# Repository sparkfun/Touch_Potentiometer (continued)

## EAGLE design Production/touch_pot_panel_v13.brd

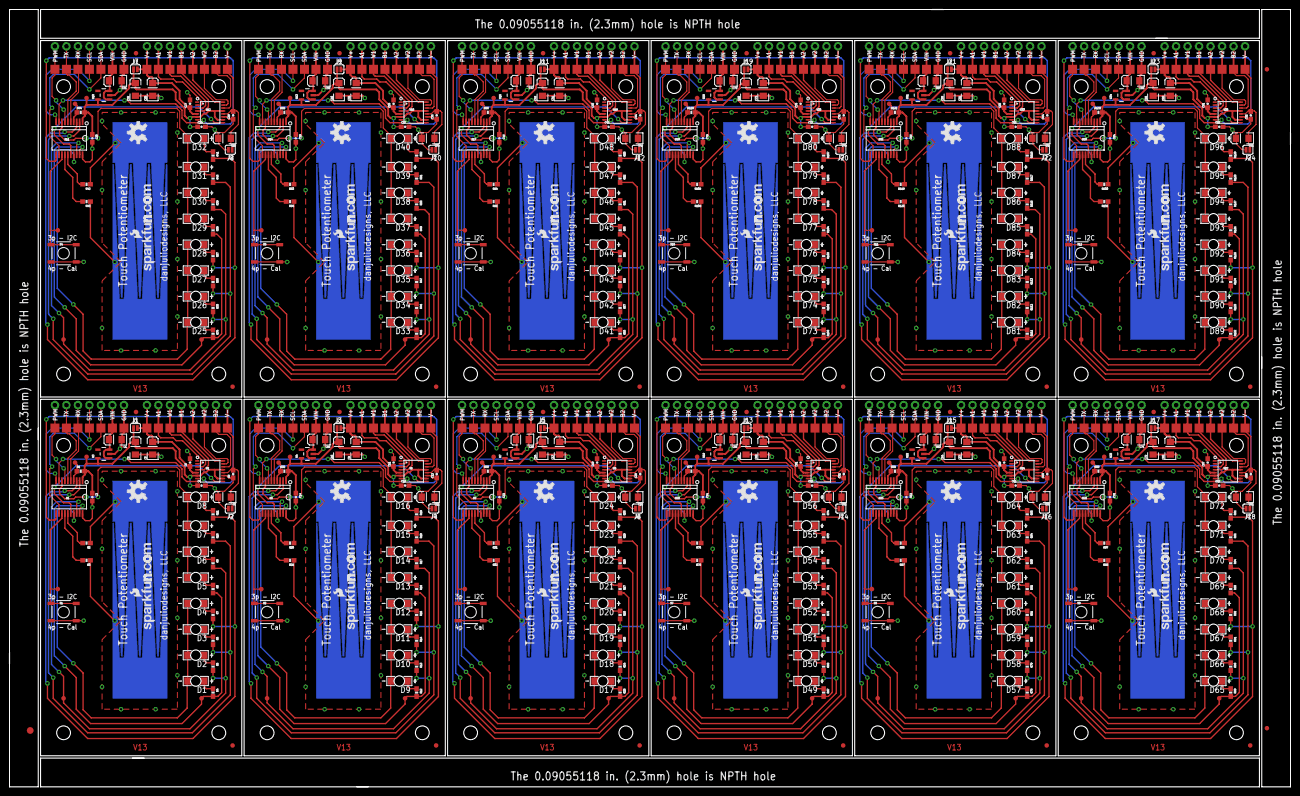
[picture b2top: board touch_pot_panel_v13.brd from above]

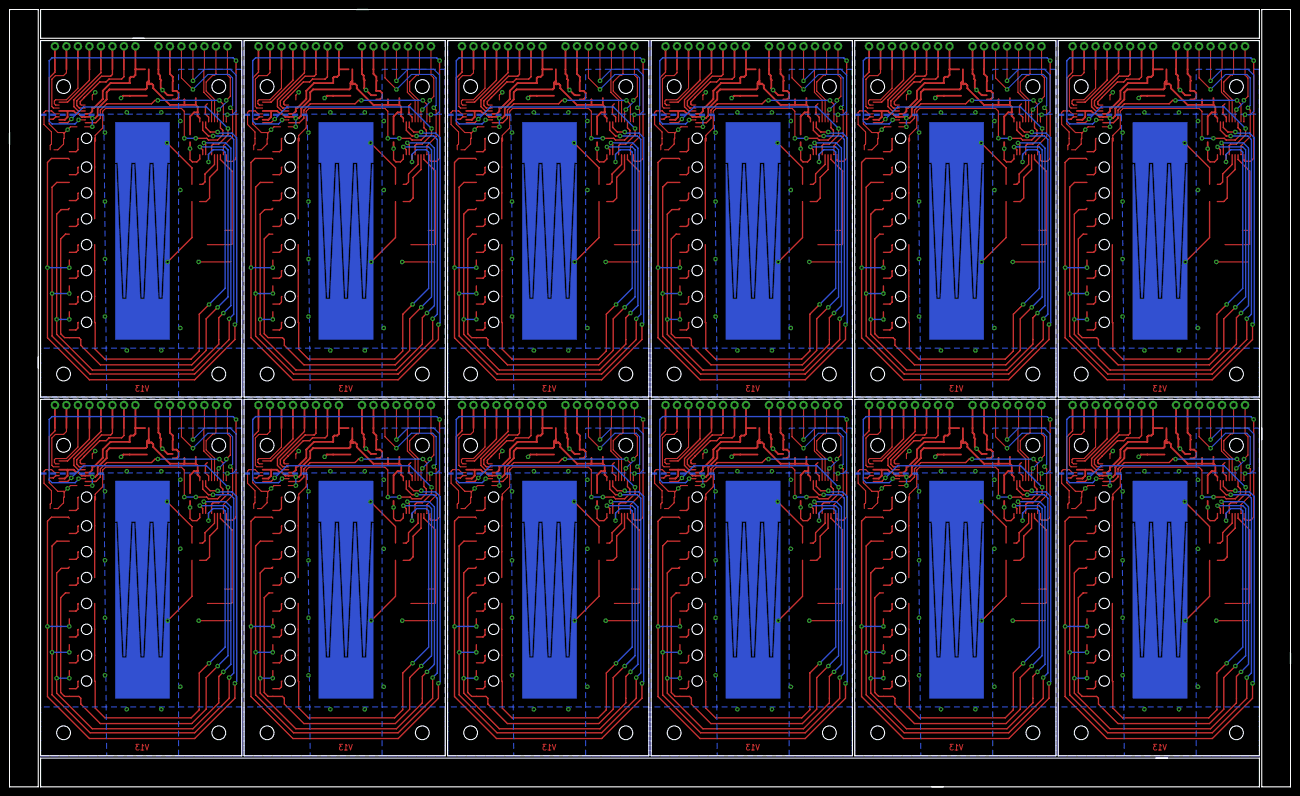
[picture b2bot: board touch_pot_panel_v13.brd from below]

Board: 2 copper layers, 283.0 x 171.7 mm, 927 parts (12 on the bottom side), 468 nets.

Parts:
C1, C2, C5, C7, C9, C10, C15, C16, C17, C18, C23, C24, C25, C26, C31, C32, C33, C34, C39, C40, C41, C42, C47, C48, C49, C50, C55, C56, C57, C58, C63, C64, C65, C66, C71, C72, C73, C74, C79, C80, C81, C82, C87, C88, C89, C90, C95, C96: 10uF; EIA3216
C3, C4, C6, C8, C11, C12, C13, C14, C19, C20, C21, C22, C27, C28, C29, C30, C35, C36, C37, C38, C43, C44, C45, C46, C51, C52, C53, C54, C59, C60, C61, C62, C67, C68, C69, C70, C75, C76, C77, C78, C83, C84, C85, C86, C91, C92, C93, C94: 0.1uF; 0603-CAP
D1, D2, D3, D4, D5, D6, D7, D8, D9, D10, D11, D12, D13, D14, D15, D16, D17, D18, D19, D20, D21, D22, D23, D24, D25, D26, D27, D28, D29, D30, D31, D32, D33, D34, D35, D36, D37, D38, D39, D40, D41, D42, D43, D44, D45, D46, D47, D48, D49, D50, D51, D52, D53, D54, D55, D56, D57, D58, D59, D60, D61, D62, D63, D64, D65, D66, D67, D68, D69, D70, D71, D72, D73, D74, D75, D76, D77, D78, D79, D80, D81, D82, D83, D84, D85, D86, D87, D88, D89, D90, D91, D92, D93, D94, D95, D96: Green; LED-1206-BOTTOM
E$1: FIDUCIAL-1.5X3
E$7, E$8: FIDUCIAL-1X2
FID1, FID2, FID3, FID4, FID5, FID6, FID7, FID8, FID9, FID10, FID11, FID12, FID13, FID14, FID15, FID16, FID17, FID18, FID19, FID20, FID21, FID22, FID23, FID24: FIDUCIAL1X2; FIDUCIAL-1X2
J1, J2, J3, J4, J5, J6, J7, J8, J9, J10, J11, J12, J13, J14, J15, J16, J17, J18, J19, J20, J21, J22, J23, J24: SJ_2S
JP1, JP2, JP3, JP4, JP5, JP6, JP7, JP8, JP9, JP10, JP11, JP12, JP13, JP14, JP15, JP16, JP17, JP18, JP19, JP20, JP21, JP22, JP23, JP24, JP25, JP26, JP27, JP28, JP29, JP30, JP31, JP32, JP33, JP34, JP35, JP36, JP37, JP38, JP39, JP40, JP41, JP42, JP43, JP44, JP45, JP46, JP47, JP48, JP49, JP50, JP51, JP52, JP53, JP54, JP55, JP56, JP57, JP58, JP59, JP60, JP61, JP62, JP63, JP64, JP65, JP66, JP67, JP68, JP69, JP70, JP71, JP72, JP73, JP74, JP75, JP76, JP77, JP78, JP79, JP80, JP81, JP82, JP83, JP84, JP85, JP86, JP87, JP88, JP89, JP90, JP91, JP92, JP93, JP94, JP95, JP96, JP97, JP98, JP99, JP100, JP101, JP102, JP103, JP104, JP105, JP106, JP107, JP108, JP109, JP110, JP111, JP112, JP113, JP114, JP115, JP116, JP117, JP118, JP119, JP120, JP121, JP122, JP123, JP124, JP125, JP126, JP127, JP128, JP129, JP130, JP131, JP132, JP133, JP134, JP135, JP136, JP137, JP138, JP139, JP140, JP141, JP142, JP143, JP144, JP145, JP146, JP147, JP148, JP149, JP150, JP151, JP152, JP153, JP154, JP155, JP156, JP157, JP158, JP159, JP160, JP161, JP162, JP163, JP164, JP165, JP166, JP167, JP168, JP169, JP170, JP171, JP172, JP173, JP174, JP175, JP176, JP177, JP178, JP179, JP180: 1X01NS
R1, R22, R33, R44, R55, R66, R77, R88, R99, R110, R121, R132: 10K; 0603-RES
R2, R3, R4, R5, R6, R7, R8, R9, R10, R11, R12, R13, R14, R15, R16, R17, R18, R19, R20, R21, R23, R24, R25, R26, R27, R28, R29, R30, R31, R32, R34, R35, R36, R37, R38, R39, R40, R41, R42, R43, R45, R46, R47, R48, R49, R50, R51, R52, R53, R54, R56, R57, R58, R59, R60, R61, R62, R63, R64, R65, R67, R68, R69, R70, R71, R72, R73, R74, R75, R76, R78, R79, R80, R81, R82, R83, R84, R85, R86, R87, R89, R90, R91, R92, R93, R94, R95, R96, R97, R98, R100, R101, R102, R103, R104, R105, R106, R107, R108, R109, R111, R112, R113, R114, R115, R116, R117, R118, R119, R120, R122, R123, R124, R125, R126, R127, R128, R129, R130, R131: 100; 0603-RES
S1, S2, S3, S4, S5, S6, S7, S8, S9, S10, S11, S12: TACTILE-SWITCH-SMD
STANDOFF1, STANDOFF2, STANDOFF3, STANDOFF4, STANDOFF5, STANDOFF6, STANDOFF7, STANDOFF8, STANDOFF9, STANDOFF10, STANDOFF11, STANDOFF12, STANDOFF13, STANDOFF14, STANDOFF15, STANDOFF16, STANDOFF17, STANDOFF18, STANDOFF19, STANDOFF20, STANDOFF21, STANDOFF22, STANDOFF23, STANDOFF24, STANDOFF25, STANDOFF26, STANDOFF27, STANDOFF28, STANDOFF29, STANDOFF30, STANDOFF31, STANDOFF32, STANDOFF33, STANDOFF34, STANDOFF35, STANDOFF36, STANDOFF37, STANDOFF38, STANDOFF39, STANDOFF40, STANDOFF41, STANDOFF42, STANDOFF43, STANDOFF44, STANDOFF45, STANDOFF46, STANDOFF47, STANDOFF48: STAND-OFFTIGHT; STAND-OFF-TIGHT
TP1, TP2, TP3, TP4, TP5, TP36, TP37, TP38, TP39, TP40, TP56, TP57, TP58, TP59, TP60, TP76, TP77, TP78, TP79, TP80, TP96, TP97, TP98, TP99, TP100, TP116, TP117, TP118, TP119, TP120, TP136, TP137, TP138, TP139, TP140, TP156, TP157, TP158, TP159, TP160, TP176, TP177, TP178, TP179, TP180, TP196, TP197, TP198, TP199, TP200, TP216, TP217, TP218, TP219, TP220, TP236, TP237, TP238, TP239, TP240: PAD.03X.04
TP6, TP7, TP8, TP9, TP10, TP11, TP12, TP13, TP14, TP15, TP16, TP17, TP18, TP19, TP20, TP21, TP22, TP23, TP24, TP25, TP26, TP27, TP28, TP29, TP30, TP31, TP32, TP33, TP34, TP35, TP41, TP42, TP43, TP44, TP45, TP46, TP47, TP48, TP49, TP50, TP51, TP52, TP53, TP54, TP55, TP61, TP62, TP63, TP64, TP65, TP66, TP67, TP68, TP69, TP70, TP71, TP72, TP73, TP74, TP75, TP81, TP82, TP83, TP84, TP85, TP86, TP87, TP88, TP89, TP90, TP91, TP92, TP93, TP94, TP95, TP101, TP102, TP103, TP104, TP105, TP106, TP107, TP108, TP109, TP110, TP111, TP112, TP113, TP114, TP115, TP121, TP122, TP123, TP124, TP125, TP126, TP127, TP128, TP129, TP130, TP131, TP132, TP133, TP134, TP135, TP141, TP142, TP143, TP144, TP145, TP146, TP147, TP148, TP149, TP150, TP151, TP152, TP153, TP154, TP155, TP161, TP162, TP163, TP164, TP165, TP166, TP167, TP168, TP169, TP170, TP171, TP172, TP173, TP174, TP175, TP181, TP182, TP183, TP184, TP185, TP186, TP187, TP188, TP189, TP190, TP191, TP192, TP193, TP194, TP195, TP201, TP202, TP203, TP204, TP205, TP206, TP207, TP208, TP209, TP210, TP211, TP212, TP213, TP214, TP215, TP221, TP222, TP223, TP224, TP225, TP226, TP227, TP228, TP229, TP230, TP231, TP232, TP233, TP234, TP235: 2MM_SMD_PAD
TS1, TS2, TS3, TS4, TS5, TS6, TS7, TS8, TS9, TS10, TS11, TS12: 2CH_48MM_LINEAR_TOUCH
U1, U5, U8, U11, U14, U17, U20, U23, U26, U29, U32, U35: PIC16F1829; SSOP20
U2, U6, U9, U12, U15, U18, U21, U24, U27, U30, U33, U36: AD5262; SSOP16
U3, U4, U7, U10, U13, U16, U19, U22, U25, U28, U31, U34: 5V; SOT23-5
U$1, U$3, U$4, U$7, U$9, U$11, U$13, U$15, U$17, U$19, U$21, U$23: OSHW-LOGOM; OSHW-LOGO-M
U$2, U$5, U$6, U$8, U$10, U$12, U$14, U$16, U$18, U$20, U$22, U$24: SFE_LOGO_NAME_WEB; SFE-NEW-WEBLOGO

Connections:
+5V: C2.A, C3.1, C4.1, J1.1, R1.2, TP2.P$1, U1.1, U2.6, U2.10, U2.13, U3.5
+5V1: C13.1, C14.1, C16.A, J3.1, R22.2, TP36.P$1, U4.5, U5.1, U6.6, U6.10, U6.13
+5V2: C21.1, C22.1, C24.A, J5.1, R33.2, TP56.P$1, U7.5, U8.1, U9.6, U9.10, U9.13
+5V3: C29.1, C30.1, C32.A, J7.1, R44.2, TP76.P$1, U10.5, U11.1, U12.6, U12.10, U12.13
+5V4: C37.1, C38.1, C40.A, J9.1, R55.2, TP96.P$1, U13.5, U14.1, U15.6, U15.10, U15.13
+5V5: C45.1, C46.1, C48.A, J11.1, R66.2, TP116.P$1, U16.5, U17.1, U18.6, U18.10, U18.13
+5V6: C53.1, C54.1, C56.A, J13.1, R77.2, TP136.P$1, U19.5, U20.1, U21.6, U21.10, U21.13
+5V7: C61.1, C62.1, C64.A, J15.1, R88.2, TP156.P$1, U22.5, U23.1, U24.6, U24.10, U24.13
+5V8: C69.1, C70.1, C72.A, J17.1, R99.2, TP176.P$1, U25.5, U26.1, U27.6, U27.10, U27.13
+5V9: C77.1, C78.1, C80.A, J19.1, R110.2, TP196.P$1, U28.5, U29.1, U30.6, U30.10, U30.13
+5V10: C85.1, C86.1, C88.A, J21.1, R121.2, TP216.P$1, U31.5, U32.1, U33.6, U33.10, U33.13
+5V11: C93.1, C94.1, C96.A, J23.1, R132.2, TP236.P$1, U34.5, U35.1, U36.6, U36.10, U36.13
A1: JP14.1, TP19.P$1, U2.2
A2: JP11.1, TP16.P$1, U2.16
A3: JP29.1, TP34.P$1, U6.2
A4: JP26.1, TP31.P$1, U6.16
A5: JP44.1, TP54.P$1, U9.2
A6: JP41.1, TP51.P$1, U9.16
A7: JP59.1, TP74.P$1, U12.2
A8: JP56.1, TP71.P$1, U12.16
A9: JP74.1, TP94.P$1, U15.2
A10: JP71.1, TP91.P$1, U15.16
A11: JP89.1, TP114.P$1, U18.2
A12: JP86.1, TP111.P$1, U18.16
A13: JP104.1, TP134.P$1, U21.2
A14: JP101.1, TP131.P$1, U21.16
A15: JP119.1, TP154.P$1, U24.2
A16: JP116.1, TP151.P$1, U24.16
A17: JP134.1, TP174.P$1, U27.2
A18: JP131.1, TP171.P$1, U27.16
A19: JP149.1, TP194.P$1, U30.2
A20: JP146.1, TP191.P$1, U30.16
A21: JP164.1, TP214.P$1, U33.2
A22: JP161.1, TP211.P$1, U33.16
A23: JP179.1, TP234.P$1, U36.2
A24: JP176.1, TP231.P$1, U36.16
AUX: S1.1, TP3.P$1, U1.13
AUX1: S2.1, TP37.P$1, U5.13
AUX2: S3.1, TP57.P$1, U8.13
AUX3: S4.1, TP77.P$1, U11.13
AUX4: S5.1, TP97.P$1, U14.13
AUX5: S6.1, TP117.P$1, U17.13
AUX6: S7.1, TP137.P$1, U20.13
AUX7: S8.1, TP157.P$1, U23.13
AUX8: S9.1, TP177.P$1, U26.13
AUX9: S10.1, TP197.P$1, U29.13
AUX10: S11.1, TP217.P$1, U32.13
AUX11: S12.1, TP237.P$1, U35.13
B1: JP12.1, TP17.P$1, U2.4
B2: JP9.1, TP14.P$1, U2.14
B3: JP27.1, TP32.P$1, U6.4
B4: JP24.1, TP29.P$1, U6.14
B5: JP42.1, TP52.P$1, U9.4
B6: JP39.1, TP49.P$1, U9.14
B7: JP57.1, TP72.P$1, U12.4
B8: JP54.1, TP69.P$1, U12.14
B9: JP72.1, TP92.P$1, U15.4
B10: JP69.1, TP89.P$1, U15.14
B11: JP87.1, TP112.P$1, U18.4
B12: JP84.1, TP109.P$1, U18.14
B13: JP102.1, TP132.P$1, U21.4
B14: JP99.1, TP129.P$1, U21.14
B15: JP117.1, TP152.P$1, U24.4
B16: JP114.1, TP149.P$1, U24.14
B17: JP132.1, TP172.P$1, U27.4
B18: JP129.1, TP169.P$1, U27.14
B19: JP147.1, TP192.P$1, U30.4
B20: JP144.1, TP189.P$1, U30.14
B21: JP162.1, TP212.P$1, U33.4
B22: JP159.1, TP209.P$1, U33.14
B23: JP177.1, TP232.P$1, U36.4
B24: JP174.1, TP229.P$1, U36.14
CPAD1: R3.2, U1.14
CPAD2: R2.2, U1.15
CPAD3: R21.2, U5.14
CPAD4: R20.2, U5.15
CPAD5: R32.2, U8.14
CPAD6: R31.2, U8.15
CPAD7: R43.2, U11.14
CPAD8: R42.2, U11.15
CPAD9: R54.2, U14.14
CPAD10: R53.2, U14.15
CPAD11: R65.2, U17.14
CPAD12: R64.2, U17.15
CPAD13: R76.2, U20.14
CPAD14: R75.2, U20.15
CPAD15: R87.2, U23.14
CPAD16: R86.2, U23.15
CPAD17: R98.2, U26.14
CPAD18: R97.2, U26.15
CPAD19: R109.2, U29.14
CPAD20: R108.2, U29.15
CPAD21: R120.2, U32.14
CPAD22: R119.2, U32.15
CPAD23: R131.2, U35.14
CPAD24: R130.2, U35.15
CSN: U1.16, U2.9
CSN1: U5.16, U6.9
CSN2: U8.16, U9.9
CSN3: U11.16, U12.9
CSN4: U14.16, U15.9
CSN5: U17.16, U18.9
CSN6: U20.16, U21.9
CSN7: U23.16, U24.9
CSN8: U26.16, U27.9
CSN9: U29.16, U30.9
CSN10: U32.16, U33.9
CSN11: U35.16, U36.9
GND: C1.C, C2.C, C3.2, C4.2, C5.C, C6.2, C7.A, C8.1, J2.1, JP7.1, S1.3, TP12.P$1, U1.20, U2.11, U3.2
GND1: C9.C, C10.A, C11.2, C12.1, C13.2, C14.2, C15.C, C16.C, J4.1, JP22.1, S2.3, TP27.P$1, U4.2, U5.20, U6.11
GND2: C17.C, C18.A, C19.2, C20.1, C21.2, C22.2, C23.C, C24.C, J6.1, JP37.1, S3.3, TP47.P$1, U7.2, U8.20, U9.11
GND3: C25.C, C26.A, C27.2, C28.1, C29.2, C30.2, C31.C, C32.C, J8.1, JP52.1, S4.3, TP67.P$1, U10.2, U11.20, U12.11
GND4: C33.C, C34.A, C35.2, C36.1, C37.2, C38.2, C39.C, C40.C, J10.1, JP67.1, S5.3, TP87.P$1, U13.2, U14.20, U15.11
GND5: C41.C, C42.A, C43.2, C44.1, C45.2, C46.2, C47.C, C48.C, J12.1, JP82.1, S6.3, TP107.P$1, U16.2, U17.20, U18.11
GND6: C49.C, C50.A, C51.2, C52.1, C53.2, C54.2, C55.C, C56.C, J14.1, JP97.1, S7.3, TP127.P$1, U19.2, U20.20, U21.11
GND7: C57.C, C58.A, C59.2, C60.1, C61.2, C62.2, C63.C, C64.C, J16.1, JP112.1, S8.3, TP147.P$1, U22.2, U23.20, U24.11
GND8: C65.C, C66.A, C67.2, C68.1, C69.2, C70.2, C71.C, C72.C, J18.1, JP127.1, S9.3, TP167.P$1, U25.2, U26.20, U27.11
GND9: C73.C, C74.A, C75.2, C76.1, C77.2, C78.2, C79.C, C80.C, J20.1, JP142.1, S10.3, TP187.P$1, U28.2, U29.20, U30.11
GND10: C81.C, C82.A, C83.2, C84.1, C85.2, C86.2, C87.C, C88.C, J22.1, JP157.1, S11.3, TP207.P$1, U31.2, U32.20, U33.11
GND11: C89.C, C90.A, C91.2, C92.1, C93.2, C94.2, C95.C, C96.C, J24.1, JP172.1, S12.3, TP227.P$1, U34.2, U35.20, U36.11
LA0: R4.2, R8.2, TP4.P$1, U1.19
LA1: R5.2, R9.2, TP5.P$1, U1.18
LA2: R6.2, R10.2, U1.2
LA3: R7.2, R11.2, U1.3
LA4: R14.2, R18.2, U5.2
LA5: R15.2, R19.2, U5.3
LA6: R13.2, R17.2, TP40.P$1, U5.18
LA7: R12.2, R16.2, TP39.P$1, U5.19
LA8: R25.2, R29.2, U8.2
LA9: R26.2, R30.2, U8.3
LA10: R24.2, R28.2, TP60.P$1, U8.18
LA11: R23.2, R27.2, TP59.P$1, U8.19
LA12: R36.2, R40.2, U11.2
LA13: R37.2, R41.2, U11.3
LA14: R35.2, R39.2, TP80.P$1, U11.18
LA15: R34.2, R38.2, TP79.P$1, U11.19
LA16: R47.2, R51.2, U14.2
LA17: R48.2, R52.2, U14.3
LA18: R46.2, R50.2, TP100.P$1, U14.18
LA19: R45.2, R49.2, TP99.P$1, U14.19
LA20: R58.2, R62.2, U17.2
LA21: R59.2, R63.2, U17.3
LA22: R57.2, R61.2, TP120.P$1, U17.18
LA23: R56.2, R60.2, TP119.P$1, U17.19
LA24: R69.2, R73.2, U20.2
LA25: R70.2, R74.2, U20.3
LA26: R68.2, R72.2, TP140.P$1, U20.18
LA27: R67.2, R71.2, TP139.P$1, U20.19
LA28: R80.2, R84.2, U23.2
LA29: R81.2, R85.2, U23.3
LA30: R79.2, R83.2, TP160.P$1, U23.18
LA31: R78.2, R82.2, TP159.P$1, U23.19
LA32: R91.2, R95.2, U26.2
LA33: R92.2, R96.2, U26.3
LA34: R90.2, R94.2, TP180.P$1, U26.18
LA35: R89.2, R93.2, TP179.P$1, U26.19
LA36: R102.2, R106.2, U29.2
LA37: R103.2, R107.2, U29.3
LA38: R101.2, R105.2, TP200.P$1, U29.18
LA39: R100.2, R104.2, TP199.P$1, U29.19
LA40: R113.2, R117.2, U32.2
LA41: R114.2, R118.2, U32.3
LA42: R112.2, R116.2, TP220.P$1, U32.18
LA43: R111.2, R115.2, TP219.P$1, U32.19
LA44: R124.2, R128.2, U35.2
LA45: R125.2, R129.2, U35.3
LA46: R123.2, R127.2, TP240.P$1, U35.18
LA47: R122.2, R126.2, TP239.P$1, U35.19
LED_PWM1: D1.C, D2.C, D3.C, D4.C, U1.17
LED_PWM2: D5.C, D6.C, D7.C, D8.C, U1.8
LED_PWM3: D9.C, D10.C, D11.C, D12.C, U5.17
LED_PWM4: D13.C, D14.C, D15.C, D16.C, U5.8
LED_PWM5: D17.C, D18.C, D19.C, D20.C, U8.17
LED_PWM6: D21.C, D22.C, D23.C, D24.C, U8.8
LED_PWM7: D25.C, D26.C, D27.C, D28.C, U11.17
LED_PWM8: D29.C, D30.C, D31.C, D32.C, U11.8
LED_PWM9: D33.C, D34.C, D35.C, D36.C, U14.17
LED_PWM10: D37.C, D38.C, D39.C, D40.C, U14.8
LED_PWM11: D41.C, D42.C, D43.C, D44.C, U17.17
LED_PWM12: D45.C, D46.C, D47.C, D48.C, U17.8
LED_PWM13: D49.C, D50.C, D51.C, D52.C, U20.17
LED_PWM14: D53.C, D54.C, D55.C, D56.C, U20.8
LED_PWM15: D57.C, D58.C, D59.C, D60.C, U23.17
LED_PWM16: D61.C, D62.C, D63.C, D64.C, U23.8
LED_PWM17: D65.C, D66.C, D67.C, D68.C, U26.17
LED_PWM18: D69.C, D70.C, D71.C, D72.C, U26.8
LED_PWM19: D73.C, D74.C, D75.C, D76.C, U29.17
LED_PWM20: D77.C, D78.C, D79.C, D80.C, U29.8
LED_PWM21: D81.C, D82.C, D83.C, D84.C, U32.17
LED_PWM22: D85.C, D86.C, D87.C, D88.C, U32.8
LED_PWM23: D89.C, D90.C, D91.C, D92.C, U35.17
LED_PWM24: D93.C, D94.C, D95.C, D96.C, U35.8
unnamed: D1.A, R4.1
unnamed: D2.A, R5.1
unnamed: D3.A, R6.1
unnamed: D4.A, R7.1
unnamed: D5.A, R8.1
unnamed: D6.A, R9.1
unnamed: D7.A, R10.1
unnamed: D8.A, R11.1
unnamed: R20.1, TS2.P$2
unnamed: R21.1, TS2.P$1
unnamed: D9.A, R12.1
unnamed: D10.A, R13.1
unnamed: D11.A, R14.1
unnamed: D12.A, R15.1
unnamed: D13.A, R16.1
unnamed: D14.A, R17.1
unnamed: D15.A, R18.1
unnamed: D16.A, R19.1
unnamed: R31.1, TS3.P$2
unnamed: R32.1, TS3.P$1
unnamed: D17.A, R23.1
unnamed: D18.A, R24.1
unnamed: D19.A, R25.1
unnamed: D20.A, R26.1
unnamed: D21.A, R27.1
unnamed: D22.A, R28.1
unnamed: D23.A, R29.1
unnamed: D24.A, R30.1
unnamed: R42.1, TS4.P$2
unnamed: R43.1, TS4.P$1
unnamed: R2.1, TS1.P$2
unnamed: R3.1, TS1.P$1
unnamed: D25.A, R34.1
unnamed: D26.A, R35.1
unnamed: D27.A, R36.1
unnamed: D28.A, R37.1
unnamed: D29.A, R38.1
unnamed: D30.A, R39.1
unnamed: D31.A, R40.1
unnamed: D32.A, R41.1
unnamed: R53.1, TS5.P$2
unnamed: R54.1, TS5.P$1
unnamed: D33.A, R45.1
unnamed: D34.A, R46.1
unnamed: D35.A, R47.1
unnamed: D36.A, R48.1
unnamed: D37.A, R49.1
unnamed: D38.A, R50.1
unnamed: D39.A, R51.1
unnamed: D40.A, R52.1
unnamed: R64.1, TS6.P$2
unnamed: R65.1, TS6.P$1
unnamed: D41.A, R56.1
unnamed: D42.A, R57.1
unnamed: D43.A, R58.1
unnamed: D44.A, R59.1
unnamed: D45.A, R60.1
unnamed: D46.A, R61.1
unnamed: D47.A, R62.1
unnamed: D48.A, R63.1
unnamed: R75.1, TS7.P$2
unnamed: R76.1, TS7.P$1
unnamed: D49.A, R67.1
unnamed: D50.A, R68.1
unnamed: D51.A, R69.1
unnamed: D52.A, R70.1
unnamed: D53.A, R71.1
unnamed: D54.A, R72.1
unnamed: D55.A, R73.1
unnamed: D56.A, R74.1
unnamed: R86.1, TS8.P$2
unnamed: R87.1, TS8.P$1
unnamed: D57.A, R78.1
unnamed: D58.A, R79.1
unnamed: D59.A, R80.1
unnamed: D60.A, R81.1
unnamed: D61.A, R82.1
unnamed: D62.A, R83.1
unnamed: D63.A, R84.1
unnamed: D64.A, R85.1
unnamed: R97.1, TS9.P$2
unnamed: R98.1, TS9.P$1
unnamed: D65.A, R89.1
unnamed: D66.A, R90.1
unnamed: D67.A, R91.1
unnamed: D68.A, R92.1
unnamed: D69.A, R93.1
unnamed: D70.A, R94.1
unnamed: D71.A, R95.1
unnamed: D72.A, R96.1
unnamed: R108.1, TS10.P$2
unnamed: R109.1, TS10.P$1
unnamed: D73.A, R100.1
unnamed: D74.A, R101.1
unnamed: D75.A, R102.1
unnamed: D76.A, R103.1
unnamed: D77.A, R104.1
unnamed: D78.A, R105.1
unnamed: D79.A, R106.1
unnamed: D80.A, R107.1
unnamed: R119.1, TS11.P$2
unnamed: R120.1, TS11.P$1
unnamed: D81.A, R111.1
unnamed: D82.A, R112.1
unnamed: D83.A, R113.1
unnamed: D84.A, R114.1
unnamed: D85.A, R115.1
unnamed: D86.A, R116.1
unnamed: D87.A, R117.1
unnamed: D88.A, R118.1
unnamed: R130.1, TS12.P$2
unnamed: R131.1, TS12.P$1
unnamed: D89.A, R122.1
unnamed: D90.A, R123.1
unnamed: D91.A, R124.1
unnamed: D92.A, R125.1
unnamed: D93.A, R126.1
unnamed: D94.A, R127.1
unnamed: D95.A, R128.1
unnamed: D96.A, R129.1
PWM_OUT: JP3.1, TP8.P$1, U1.7
PWM_OUT1: JP18.1, TP23.P$1, U5.7
PWM_OUT2: JP33.1, TP43.P$1, U8.7
PWM_OUT3: JP48.1, TP63.P$1, U11.7
PWM_OUT4: JP63.1, TP83.P$1, U14.7
PWM_OUT5: JP78.1, TP103.P$1, U17.7
PWM_OUT6: JP93.1, TP123.P$1, U20.7
PWM_OUT7: JP108.1, TP143.P$1, U23.7
PWM_OUT8: JP123.1, TP163.P$1, U26.7
PWM_OUT9: JP138.1, TP183.P$1, U29.7
PWM_OUT10: JP153.1, TP203.P$1, U32.7
PWM_OUT11: JP168.1, TP223.P$1, U35.7
RX: JP4.1, TP9.P$1, U1.5
RX1: JP19.1, TP24.P$1, U5.5
RX2: JP34.1, TP44.P$1, U8.5
RX3: JP49.1, TP64.P$1, U11.5
RX4: JP64.1, TP84.P$1, U14.5
RX5: JP79.1, TP104.P$1, U17.5
RX6: JP94.1, TP124.P$1, U20.5
RX7: JP109.1, TP144.P$1, U23.5
RX8: JP124.1, TP164.P$1, U26.5
RX9: JP139.1, TP184.P$1, U29.5
RX10: JP154.1, TP204.P$1, U32.5
RX11: JP169.1, TP224.P$1, U35.5
SCL: JP2.1, TP7.P$1, U1.10
SCL1: JP17.1, TP22.P$1, U5.10
SCL2: JP32.1, TP42.P$1, U8.10
SCL3: JP47.1, TP62.P$1, U11.10
SCL4: JP62.1, TP82.P$1, U14.10
SCL5: JP77.1, TP102.P$1, U17.10
SCL6: JP92.1, TP122.P$1, U20.10
SCL7: JP107.1, TP142.P$1, U23.10
SCL8: JP122.1, TP162.P$1, U26.10
SCL9: JP137.1, TP182.P$1, U29.10
SCL10: JP152.1, TP202.P$1, U32.10
SCL11: JP167.1, TP222.P$1, U35.10
SCLK: U1.11, U2.7
SCLK1: U5.11, U6.7
SCLK2: U8.11, U9.7
SCLK3: U11.11, U12.7
SCLK4: U14.11, U15.7
SCLK5: U17.11, U18.7
SCLK6: U20.11, U21.7
SCLK7: U23.11, U24.7
SCLK8: U26.11, U27.7
SCLK9: U29.11, U30.7
SCLK10: U32.11, U33.7
SCLK11: U35.11, U36.7
SDA: JP1.1, TP6.P$1, U1.12
SDA1: JP16.1, TP21.P$1, U5.12
SDA2: JP31.1, TP41.P$1, U8.12
SDA3: JP46.1, TP61.P$1, U11.12
SDA4: JP61.1, TP81.P$1, U14.12
SDA5: JP76.1, TP101.P$1, U17.12
SDA6: JP91.1, TP121.P$1, U20.12
SDA7: JP106.1, TP141.P$1, U23.12
SDA8: JP121.1, TP161.P$1, U26.12
SDA9: JP136.1, TP181.P$1, U29.12
SDA10: JP151.1, TP201.P$1, U32.12
SDA11: JP166.1, TP221.P$1, U35.12
SDO: U1.9, U2.8
SDO1: U5.9, U6.8
SDO2: U8.9, U9.8
SDO3: U11.9, U12.8
SDO4: U14.9, U15.8
SDO5: U17.9, U18.8
SDO6: U20.9, U21.8
SDO7: U23.9, U24.8
SDO8: U26.9, U27.8
SDO9: U29.9, U30.8
SDO10: U32.9, U33.8
SDO11: U35.9, U36.8
TX: JP5.1, TP10.P$1, U1.6
TX1: JP20.1, TP25.P$1, U5.6
TX2: JP35.1, TP45.P$1, U8.6
TX3: JP50.1, TP65.P$1, U11.6
TX4: JP65.1, TP85.P$1, U14.6
TX5: JP80.1, TP105.P$1, U17.6
TX6: JP95.1, TP125.P$1, U20.6
TX7: JP110.1, TP145.P$1, U23.6
TX8: JP125.1, TP165.P$1, U26.6
TX9: JP140.1, TP185.P$1, U29.6
TX10: JP155.1, TP205.P$1, U32.6
TX11: JP170.1, TP225.P$1, U35.6
V+: C5.A, C6.1, J1.2, JP15.1, TP20.P$1, U2.5
V+1: C9.A, C11.1, J3.2, JP30.1, TP35.P$1, U6.5
V+2: C17.A, C19.1, J5.2, JP45.1, TP55.P$1, U9.5
V+3: C25.A, C27.1, J7.2, JP60.1, TP75.P$1, U12.5
V+4: C33.A, C35.1, J9.2, JP75.1, TP95.P$1, U15.5
V+5: C41.A, C43.1, J11.2, JP90.1, TP115.P$1, U18.5
V+6: C49.A, C51.1, J13.2, JP105.1, TP135.P$1, U21.5
V+7: C57.A, C59.1, J15.2, JP120.1, TP155.P$1, U24.5
V+8: C65.A, C67.1, J17.2, JP135.1, TP175.P$1, U27.5
V+9: C73.A, C75.1, J19.2, JP150.1, TP195.P$1, U30.5
V+10: C81.A, C83.1, J21.2, JP165.1, TP215.P$1, U33.5
V+11: C89.A, C91.1, J23.2, JP180.1, TP235.P$1, U36.5
V-: C7.C, C8.2, J2.2, JP8.1, TP13.P$1, U2.12
V-1: C10.C, C12.2, J4.2, JP23.1, TP28.P$1, U6.12
V-2: C18.C, C20.2, J6.2, JP38.1, TP48.P$1, U9.12
V-3: C26.C, C28.2, J8.2, JP53.1, TP68.P$1, U12.12
V-4: C34.C, C36.2, J10.2, JP68.1, TP88.P$1, U15.12
V-5: C42.C, C44.2, J12.2, JP83.1, TP108.P$1, U18.12
V-6: C50.C, C52.2, J14.2, JP98.1, TP128.P$1, U21.12
V-7: C58.C, C60.2, J16.2, JP113.1, TP148.P$1, U24.12
V-8: C66.C, C68.2, J18.2, JP128.1, TP168.P$1, U27.12
V-9: C74.C, C76.2, J20.2, JP143.1, TP188.P$1, U30.12
V-10: C82.C, C84.2, J22.2, JP158.1, TP208.P$1, U33.12
V-11: C90.C, C92.2, J24.2, JP173.1, TP228.P$1, U36.12
VIN: C1.A, JP6.1, TP11.P$1, U3.1, U3.3
VIN1: C15.A, JP21.1, TP26.P$1, U4.1, U4.3
VIN2: C23.A, JP36.1, TP46.P$1, U7.1, U7.3
VIN3: C31.A, JP51.1, TP66.P$1, U10.1, U10.3
VIN4: C39.A, JP66.1, TP86.P$1, U13.1, U13.3
VIN5: C47.A, JP81.1, TP106.P$1, U16.1, U16.3
VIN6: C55.A, JP96.1, TP126.P$1, U19.1, U19.3
VIN7: C63.A, JP111.1, TP146.P$1, U22.1, U22.3
VIN8: C71.A, JP126.1, TP166.P$1, U25.1, U25.3
VIN9: C79.A, JP141.1, TP186.P$1, U28.1, U28.3
VIN10: C87.A, JP156.1, TP206.P$1, U31.1, U31.3
VIN11: C95.A, JP171.1, TP226.P$1, U34.1, U34.3
VPP: R1.1, TP1.P$1, U1.4
VPP1: R22.1, TP38.P$1, U5.4
VPP2: R33.1, TP58.P$1, U8.4
VPP3: R44.1, TP78.P$1, U11.4
VPP4: R55.1, TP98.P$1, U14.4
VPP5: R66.1, TP118.P$1, U17.4
VPP6: R77.1, TP138.P$1, U20.4
VPP7: R88.1, TP158.P$1, U23.4
VPP8: R99.1, TP178.P$1, U26.4
VPP9: R110.1, TP198.P$1, U29.4
VPP10: R121.1, TP218.P$1, U32.4
VPP11: R132.1, TP238.P$1, U35.4
W1: JP13.1, TP18.P$1, U2.3
W2: JP10.1, TP15.P$1, U2.15
W3: JP28.1, TP33.P$1, U6.3
W4: JP25.1, TP30.P$1, U6.15
W5: JP43.1, TP53.P$1, U9.3
W6: JP40.1, TP50.P$1, U9.15
W7: JP58.1, TP73.P$1, U12.3
W8: JP55.1, TP70.P$1, U12.15
W9: JP73.1, TP93.P$1, U15.3
W10: JP70.1, TP90.P$1, U15.15
W11: JP88.1, TP113.P$1, U18.3
W12: JP85.1, TP110.P$1, U18.15
W13: JP103.1, TP133.P$1, U21.3
W14: JP100.1, TP130.P$1, U21.15
W15: JP118.1, TP153.P$1, U24.3
W16: JP115.1, TP150.P$1, U24.15
W17: JP133.1, TP173.P$1, U27.3
W18: JP130.1, TP170.P$1, U27.15
W19: JP148.1, TP193.P$1, U30.3
W20: JP145.1, TP190.P$1, U30.15
W21: JP163.1, TP213.P$1, U33.3
W22: JP160.1, TP210.P$1, U33.15
W23: JP178.1, TP233.P$1, U36.3
W24: JP175.1, TP230.P$1, U36.15

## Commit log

2014-06-13 Initial Commit
    Committing files given to me by Dan Julio. Will be working to scrub the
    design, switch out parts for SFE parts, and figure out what parts will
    need to be ordered and added to inventory.
2014-06-13 Fixed Frame
    Added the correct frame on schematic and moved around testbed files
2014-07-02 First Round of changes before Protos
    Changed Dimension thickness
    Changed silk ratio
    Added designed by name
    Bumped via size up to 0.020
    Added actual stand-offs instead of drill hits
    Labeled push button
2014-08-30 Work in progress
    rerouting for fourth standoff hole
2014-09-22 Last commit before protos
    Finally rerouted to add space for fourth stand-off hole.
2014-10-31 Fixing weird file glitchs
2014-11-10 2nd Round of Protos
    Added a few test points, moved a cap closer to analog IC, moved button
    down to avoid touching resistors.
2014-11-13 adding back gitingnore
    adding back gitingnore
2014-11-13 Final commit before 2nd round of protos - 4 real
    made all test points the same size, trace clean up, moved filtering cap
    as close as possible.
2014-11-13 Schematic Cleanup
    added flags, added I2C and VIN Info, general cleanup
2014-11-21 Changed all parts to SFE parts with SKUs
    Changed all parts to SFE parts with SKUs
2014-11-26 Last push before second round of protos 4 Realz
    Lots of QC checklist changes, added parts to SFE library,
    isolate, schematic cleanup, added all SFE parts with SKUs.
2015-01-05 Changed pinout to standard I2C pinout
    Changed pinout to standard I2C pinout
2015-01-07 Ready for Reds
    Added note about Non-plated Thru Holes on the bottom-mounted LEDs,
    added note about I2C addressing, added note about maximum and min.
    voltages on V+ and V-, moved VPP test point ever so slightly, added
    polarity silk to bottom-mounted LEDs, added note in Sparkle about BLACK
    SOLDERMASK.
2015-01-21 replaced fids with SFE fids
2015-01-21 created panel v12
2015-05-08 V13 Changes
    Adjusted headers to fit on breadboard. Minor rerouting. Moved silk.
2015-05-08 V13
    v13
2015-05-29 Adjusting PTH for breadboard
    Adjusted the PTH holes to fit into a breadboard. Dan has completed
    major firmware updates. Can now calibrate ion the fly with push button.
    Moved PTH holes to end of PCB and silk in-between PTH and SMD pads.
2015-06-02 Clean-up, change button text
    Moved traces away from hole, deleted unused ground traces, resized one
    trace, changed button text for both i2c and cal.
2015-07-10 Last QC Check changes
    Minor changes based on QC Checklist.
2015-09-01 created panel v13
2015-09-01 removed odd ground line
2015-10-23 Adding Documentation folder
